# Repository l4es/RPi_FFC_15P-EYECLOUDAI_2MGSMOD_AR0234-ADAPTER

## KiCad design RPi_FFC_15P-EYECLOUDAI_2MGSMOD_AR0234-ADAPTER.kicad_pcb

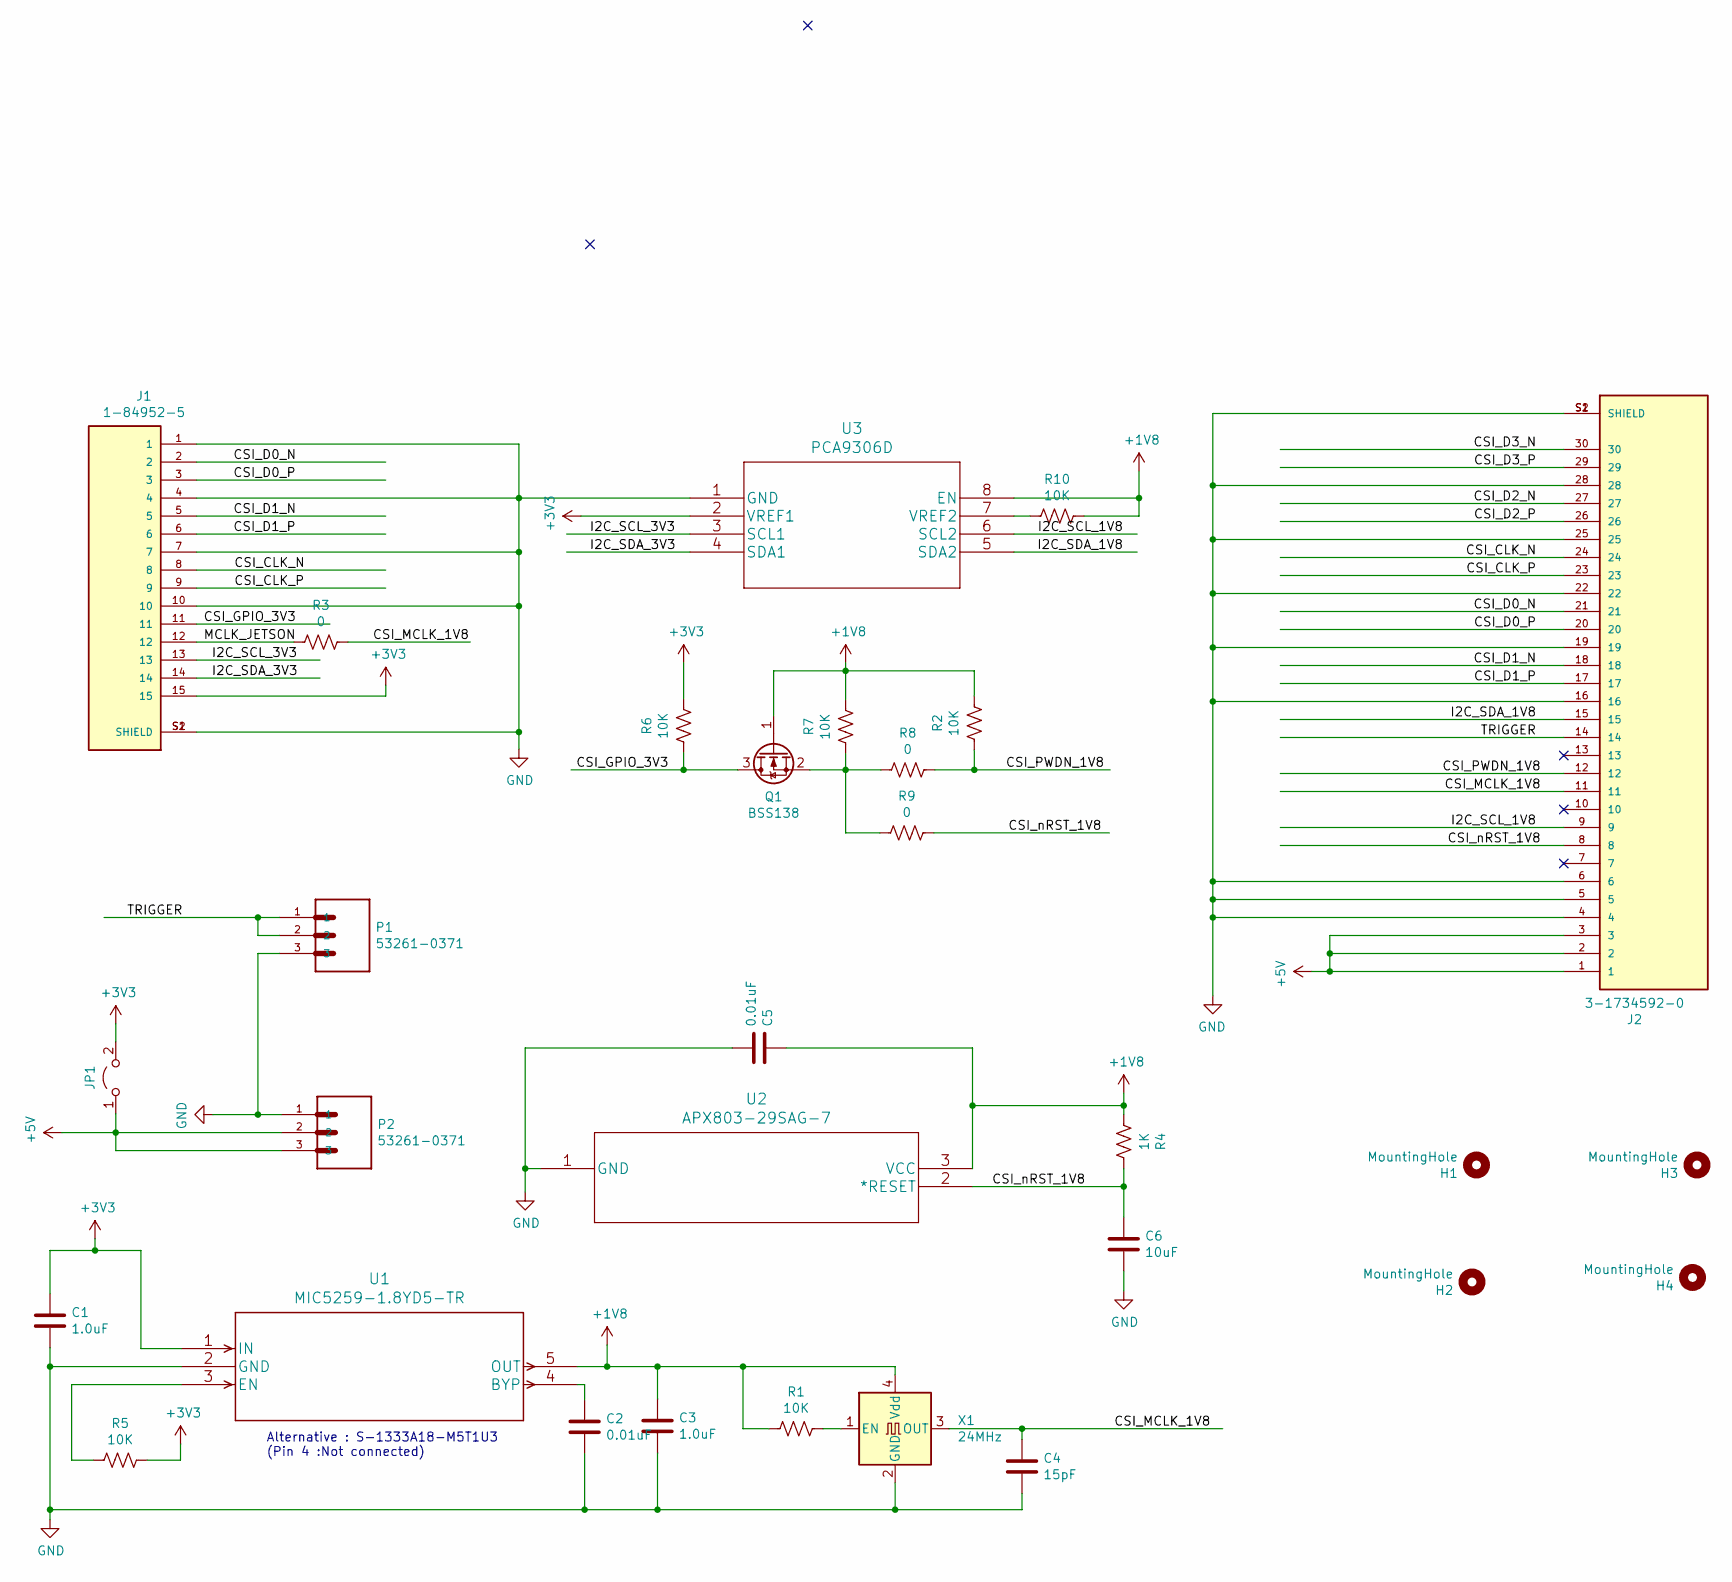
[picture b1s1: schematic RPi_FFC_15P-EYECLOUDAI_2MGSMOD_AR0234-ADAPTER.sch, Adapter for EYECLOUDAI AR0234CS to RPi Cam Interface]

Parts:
C1, C3: 1.0uF; C_0603_1608Metric_Pad1.08x0.95mm_HandSolder
C2, C5: 0.01uF; C_0603_1608Metric_Pad1.08x0.95mm_HandSolder
C4: 15pF; C_0603_1608Metric_Pad1.08x0.95mm_HandSolder
C6: 10uF; C_0603_1608Metric_Pad1.08x0.95mm_HandSolder
H1, H2, H3, H4: MountingHole; MountingHole_2.2mm_M2_Pad
J1: 1-84952-5; TE_1-84952-5; PARTREV A4; DigiKey_Part_Number A101391TR-ND
J2: 3-1734592-0; TE_3-1734592-0; PARTREV C
JP1: Jumper_3V3; SolderJumper-2_P1.3mm_Open_RoundedPad1.0x1.5mm
P1, P2: 53261-0371; MOLEX_53261-0371
Q1: BSS138; SOT-23
R1, R2, R5, R6, R7, R10: 10K; R_0603_1608Metric_Pad0.98x0.95mm_HandSolder
R3, R8, R9: 0; R_0603_1608Metric_Pad0.98x0.95mm_HandSolder
R4: 1K; R_0603_1608Metric_Pad0.98x0.95mm_HandSolder
U1: MIC5259-1.8YD5-TR; MIC5259-2.8YD5-TR
U2: APX803-29SAG-7
U3: PCA9306D
X1: 24MHz; Oscillator_SMD_TXC_7C-4Pin_5.0x3.2mm

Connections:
+1V8: C3.1, C5.1, Q1.1 (G), R1.2, R2.1, R4.2, R7.1, R10.1, U1.5 (OUT), U2.3 (VCC), U3.8 (EN), X1.4 (Vdd)
+3V3: C1.1, J1.15, JP1.2 (B), R5.1, R6.1, U1.1 (IN), U3.2 (VREF1)
+5V: J2.1, J2.2, J2.3, JP1.1 (A), P2.2, P2.3
/CSI_CLK_N: J1.8, J2.24
/CSI_CLK_P: J1.9, J2.23
/CSI_D0_N: J1.2, J2.21
/CSI_D0_P: J1.3, J2.20
/CSI_D1_N: J1.5, J2.18
/CSI_D1_P: J1.6, J2.17
/CSI_D2_N: J2.27
/CSI_D2_P: J2.26
/CSI_D3_N: J2.30
/CSI_D3_P: J2.29
/CSI_GPIO_3V3: J1.11, Q1.3 (D), R6.2
/CSI_MCLK_1V8: C4.1, J2.11, R3.1, X1.3 (OUT)
/CSI_PWDN_1V8: J2.12, R2.2, R8.1
/CSI_nRST_1V8: C6.1, J2.8, R4.1, R9.1, U2.2 (*RESET)
/I2C_SCL_1V8: J2.9, U3.6 (SCL2)
/I2C_SCL_3V3: J1.13, U3.3 (SCL1)
/I2C_SDA_1V8: J2.15, U3.5 (SDA2)
/I2C_SDA_3V3: J1.14, U3.4 (SDA1)
/MCLK_JETSON: J1.12, R3.2
/TRIGGER: J2.14, P1.1, P1.2
GND: C1.2, C2.2, C3.2, C4.2, C5.2, C6.2, J1.1, J1.4, J1.7, J1.10, J1.S1 (SHIELD), J1.S2 (SHIELD), J2.4, J2.5, J2.6, J2.16, J2.19, J2.22, J2.25, J2.28, J2.S1 (SHIELD), J2.S2 (SHIELD), P1.3, P2.1, U1.2 (GND), U2.1 (GND), U3.1 (GND), X1.2 (GND)
unnamed: C2.1, U1.4 (BYP)
unnamed: Q1.2 (S), R7.2, R8.2, R9.2
unnamed: R1.1, X1.1 (EN)
unnamed: R5.2, U1.3 (EN)
unnamed: R10.2, U3.7 (VREF2)

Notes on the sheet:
Alternative : S-1333A18-M5T1U3 (Pin 4 :Not connected)

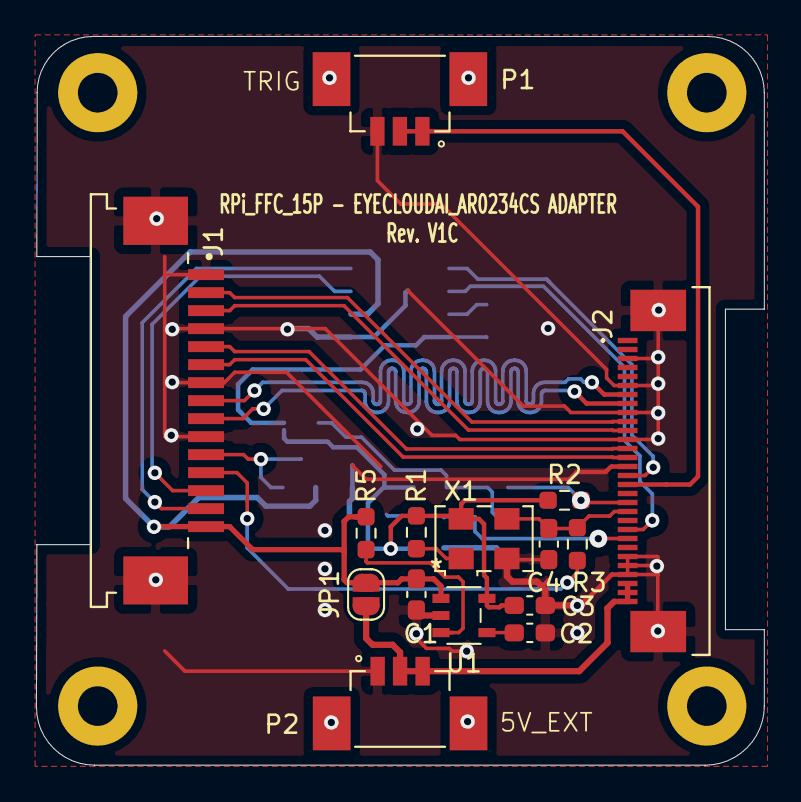
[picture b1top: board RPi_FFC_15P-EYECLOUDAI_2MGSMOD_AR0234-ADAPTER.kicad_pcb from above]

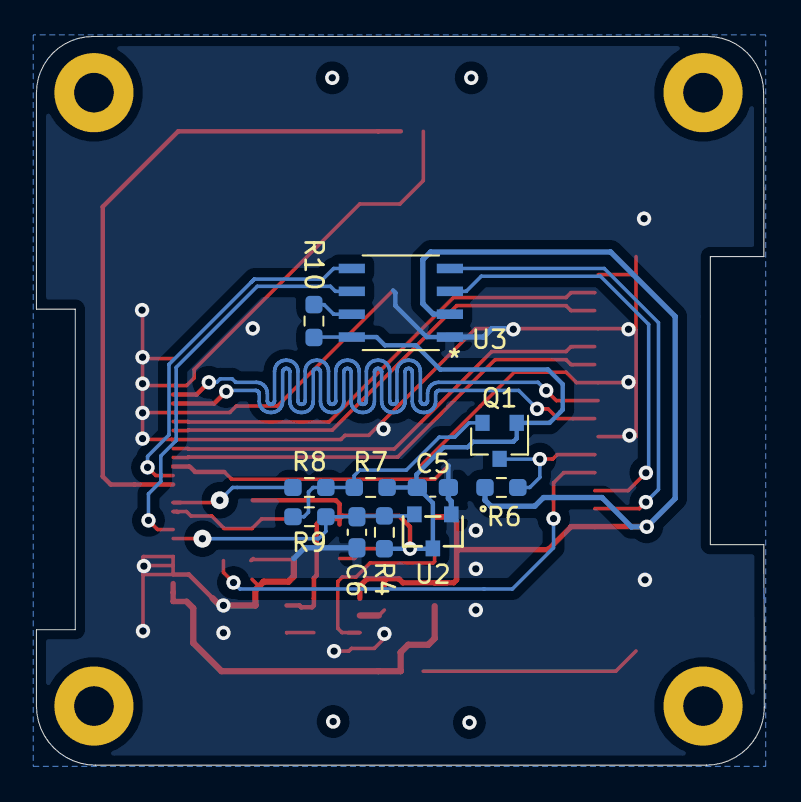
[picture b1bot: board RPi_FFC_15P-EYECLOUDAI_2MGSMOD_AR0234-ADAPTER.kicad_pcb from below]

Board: 2 copper layers, 40.4 x 40.5 mm, 30 parts (11 on the bottom side), 25 nets.

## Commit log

2023-10-16 Add intial commit
2023-10-21 Add level shifters for 3V3<->1V8 signals
2024-08-11 Add schematic of V1B
2024-08-11 Add V1C
    Add 15pF capacitor at the ouput pin of the oscillator.
2024-08-11 Update PCB design due to forget saving before commit

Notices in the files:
parts and their libraries:
Copyright 2021 Accelerated Designs. All rights reserved.
Copyright 2016 Accelerated Designs. All rights reserved.
